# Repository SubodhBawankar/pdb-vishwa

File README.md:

# pdb-vishwa
# Power Distribution Board for Vishwa Rover 2024

The circuitry converts voltage from batteries to a specific voltage using voltage regulators and switching regulators. Adjustable voltage converters are used to convert 12V to 5V, 3.7V, and 3.3V. Switching buck-boost converters are used to obtain 7V, 9V, and 24V from 12V. All this circuitry is integrated into a single Printed Circuit Board.

[Components List](https://docs.google.com/spreadsheets/d/1e5Fw-HEnwtgFm58ctA9HxLs7_NTRD_BNhpObLu1VbHM/edit?usp=sharing)

### Images: 
Connections:

3D View:

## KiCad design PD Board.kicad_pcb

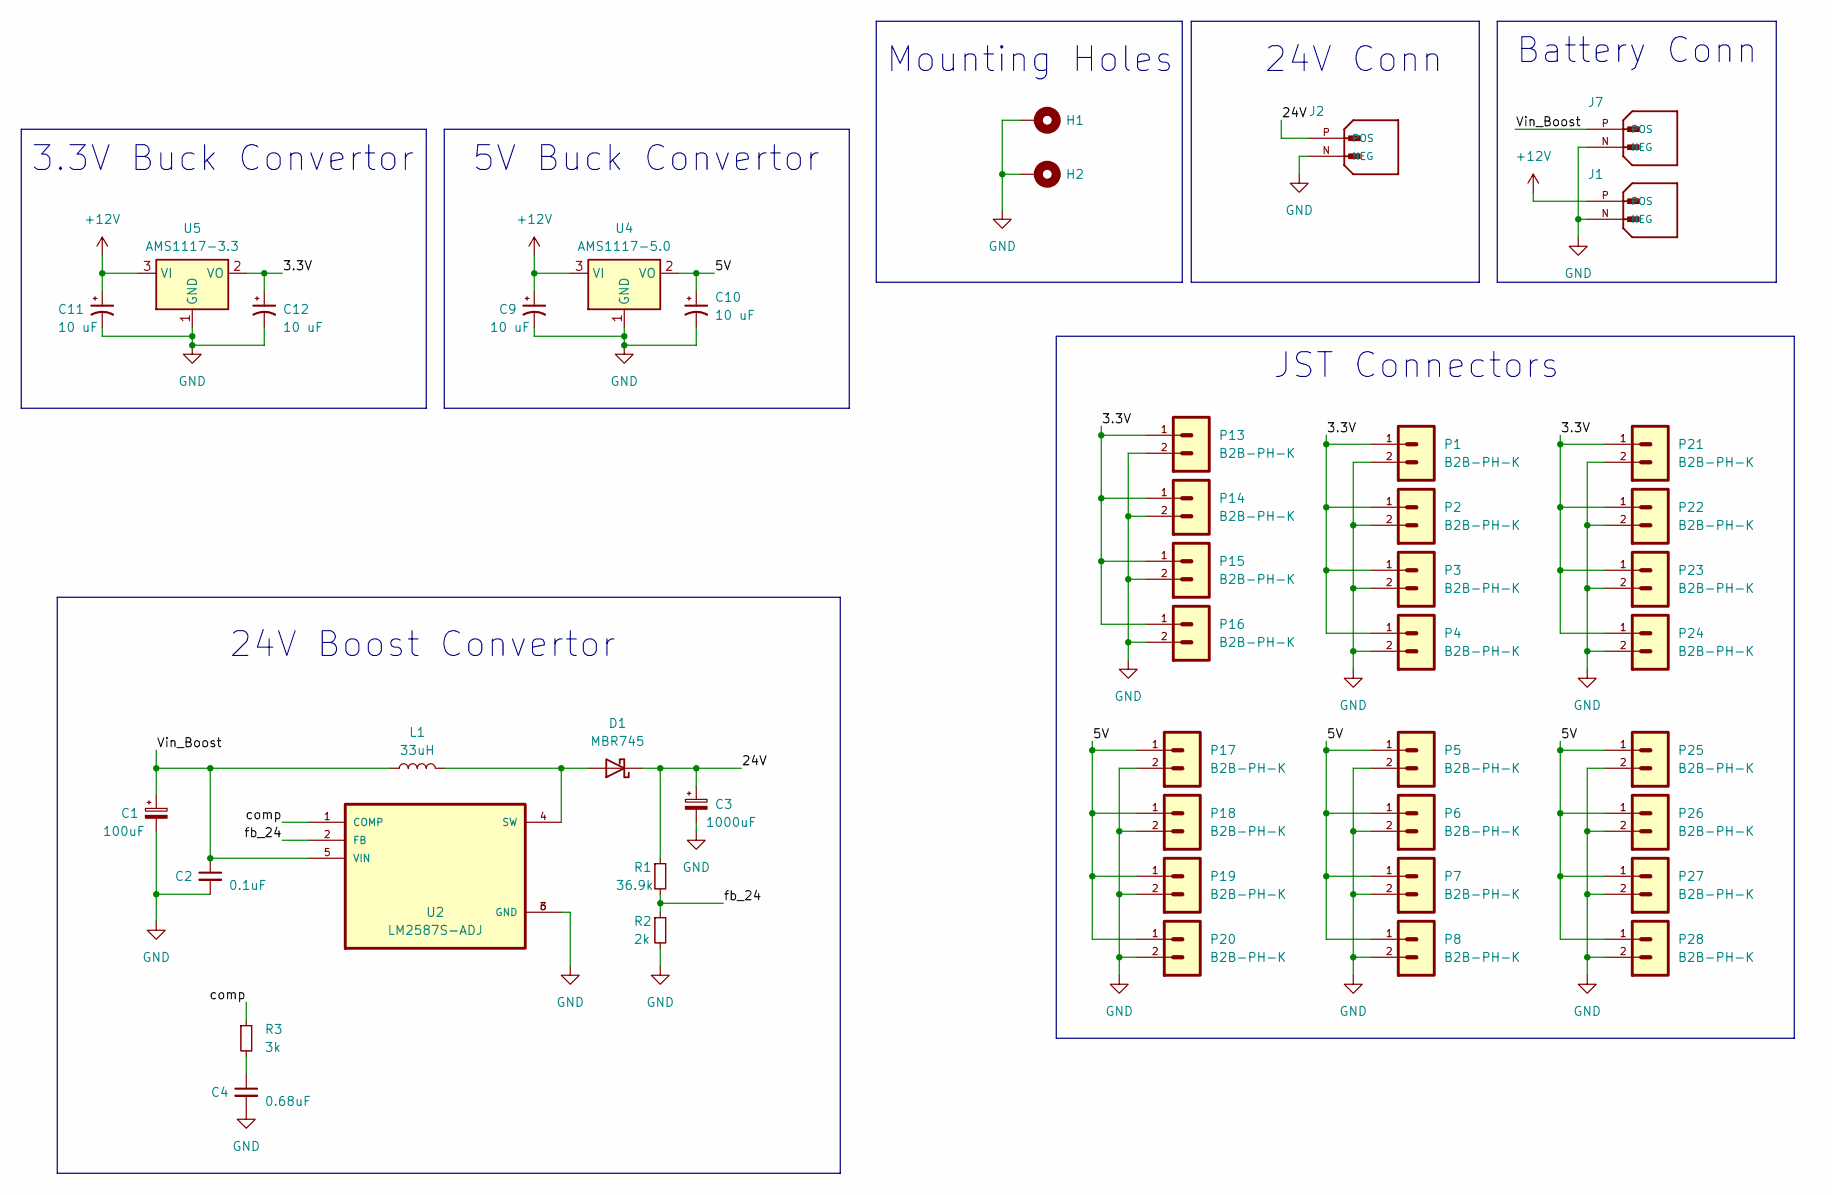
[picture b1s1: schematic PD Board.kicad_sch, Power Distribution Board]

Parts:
C1: 100uF; CP_Elec_6.3x7.7
C2: 0.1uF; C_0805_2012Metric
C3: 1000uF; CP_Radial_D10.0mm_P5.00mm
C4: 0.68uF; C_0805_2012Metric
C9, C10, C11, C12: 10 uF; C_0805_2012Metric
D1: MBR745; D_SMC
H1, H2: MountingHole_Pad; MountingHole_2.2mm_M2_Pad_Via
J1, J2, J7: XT60PW-M; AMASS_XT60-M; PARTREV V1.2
L1: 33uH; L_Bourns_SRP7028A_7.3x6.6mm
P1, P2, P3, P4, P5, P6, P7, P8, P13, P14, P15, P16, P17, P18, P19, P20, P21, P22, P23, P24, P25, P26, P27, P28: B2B-PH-K; JST_PH_B2B-PH-K_1x02_P2.00mm_Vertical
R1: 36.9k; R_1206_3216Metric
R2: 2k; R_1206_3216Metric
R3: 3k; R_1206_3216Metric
U2: LM2587S-ADJ; VREG_TPS79625KTTR
U4: AMS1117-5.0; SOT-223-3_TabPin2
U5: AMS1117-3.3; SOT-223-3_TabPin2

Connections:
+12V: C9.1, C11.1, J1.P (POS), U4.3 (VI), U5.3 (VI)
/3.3V: C12.1, P1.1, P2.1, P3.1, P4.1, P13.1, P14.1, P15.1, P16.1, P21.1, P22.1, P23.1, P24.1, U5.2 (VO)
/5V: C10.1, P5.1, P6.1, P7.1, P8.1, P17.1, P18.1, P19.1, P20.1, P25.1, P26.1, P27.1, P28.1, U4.2 (VO)
/24V: C3.1, D1.1 (K), J2.P (POS), R1.1
/Vin_Boost: C1.1, C2.1, J7.P (POS), L1.1, U2.5 (VIN)
/comp: R3.1, U2.1 (COMP)
/fb_24: R1.2, R2.1, U2.2 (FB)
GND: C1.2, C2.2, C3.2, C4.2, C9.2, C10.2, C11.2, C12.2, H1.1, H2.1, J1.N (NEG), J2.N (NEG), J7.N (NEG), P1.2, P2.2, P3.2, P4.2, P5.2, P6.2, P7.2, P8.2, P13.2, P14.2, P15.2, P16.2, P17.2, P18.2, P19.2, P20.2, P21.2, P22.2, P23.2, P24.2, P25.2, P26.2, P27.2, P28.2, R2.2, U2.3 (GND), U2.6 (GND), U4.1 (GND), U5.1 (GND)
unnamed: C4.1, R3.2
unnamed: D1.2 (A), L1.2, U2.4 (SW)

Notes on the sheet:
Battery Conn
24V Conn
5V Buck Convertor
Mounting Holes
JST Connectors
24V Boost Convertor
3.3V Buck Convertor

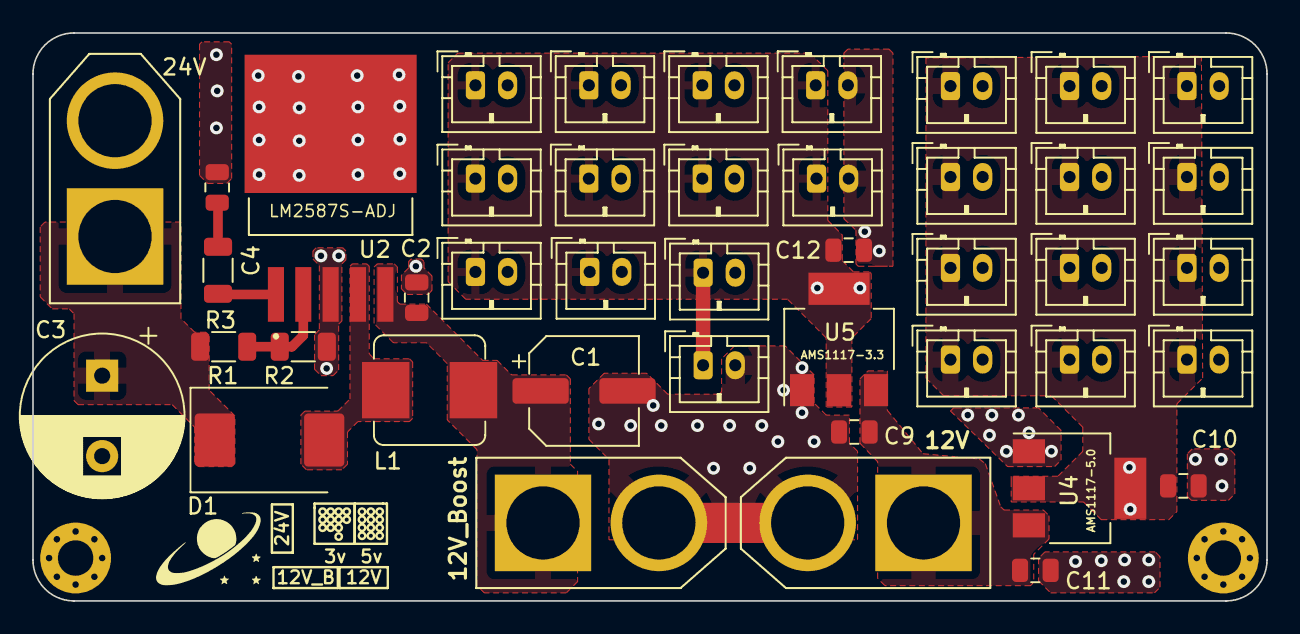
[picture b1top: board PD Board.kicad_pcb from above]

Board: 2 copper layers, 76.7 x 35.3 mm, 45 parts (0 on the bottom side), 10 nets.

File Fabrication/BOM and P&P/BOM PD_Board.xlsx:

Comment | Designator | Footprint | Quantity | JLCPCB Part # | Digikey Mgf #
2k | R2 | R_1206_3216Metric | 1 | C17944 | ESR18EZPF2001
33uH | L1 | L_Bourns_SRP7028A_7.3x6.6mm | 1 | C2046760 | SRP7028A-330M
36.9k | R1 | R_1206_3216Metric | 1 | C205346 | RC1206FR-0736K5L
AMS1117-3.3 | U5 | SOT-223-3_TabPin2 | 1 | C5250992 | 4518-AMS1117-3.3CT-ND
0.1uF | C2 | C_0805_2012Metric | 1 | C6641151 | C2012X7T2E104K125AE
0.68uF | C4 | C_0805_2012Metric | 1 | C520000 | C0805C684K5RAC7800
100uF | C1 | CP_Elec_6.3x7.7 | 1 | C5253633 | UCL1V101MCL6GS
1000uF | C3 | CP_Radial_D10.0mm_P5.00mm | 1 | C136014 | 35PX1000MEFC10X20
MBR745 | D1 | D_SMC | 1 | C524830 | SK56L-TP
10 uF | C11,C9,C10,C12 | C_0805_2012Metric | 4 | C162422 | GRM21BR61E106KA73L
3k | R3 | R_1206_3216Metric | 1 | C205286 | RC1206JR-073KL
AMS1117-5.0 | U4 | SOT-223-3_TabPin2 | 1 | C347223 | AZ1117IH-5.0TRG1
LM2587S-ADJ | U2 | VREG_TPS79625KTTR | 1 | C1355343 | LM2587SX-ADJ/NOPB
B2B-PH-K | P16,P19,P7,P24,P26,P13,P17,P21,P25,P23,P4,P22,P14,P28,P27,P2,P1,P5,P18,P3,P15,P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 | JST_PH_B2B-PH-K_1x02_P2.00mm_Vertical | 24 | C131337 | B2B-PH-K-S
XT60PW-M | J1,J2,J7 | AMASS_XT60-M | 3 | C98733 | PRT-10474
MountingHole_Pad | H2,H1 | MountingHole_2.2mm_M2_Pad_Via | 2

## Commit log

2023-10-30 Uploading V02
2023-12-05 Deleting Old Files
2023-12-05 Final Board Upload
